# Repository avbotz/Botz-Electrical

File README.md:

# Botz-Electrical
PCBs and anything else electrical may want to leave for posterity.

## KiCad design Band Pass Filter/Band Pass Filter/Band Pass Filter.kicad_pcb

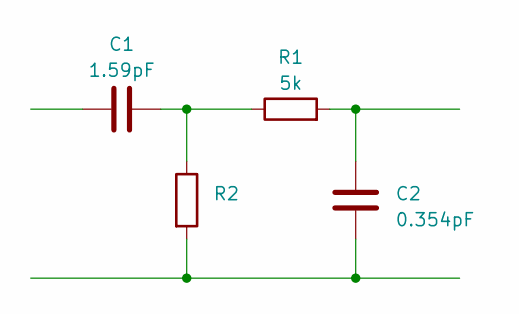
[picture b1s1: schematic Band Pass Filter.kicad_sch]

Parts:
C1: 1.59pF
C2: 0.354pF
R1, R2: 5k

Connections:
unnamed: C1.2, R1.1, R2.1
unnamed: C2.1, R1.2
unnamed: C2.2, R2.2

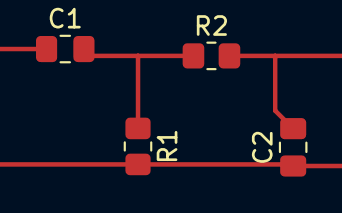
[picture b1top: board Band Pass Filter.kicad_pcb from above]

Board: 2 copper layers, 4 parts (0 on the bottom side), 3 nets.

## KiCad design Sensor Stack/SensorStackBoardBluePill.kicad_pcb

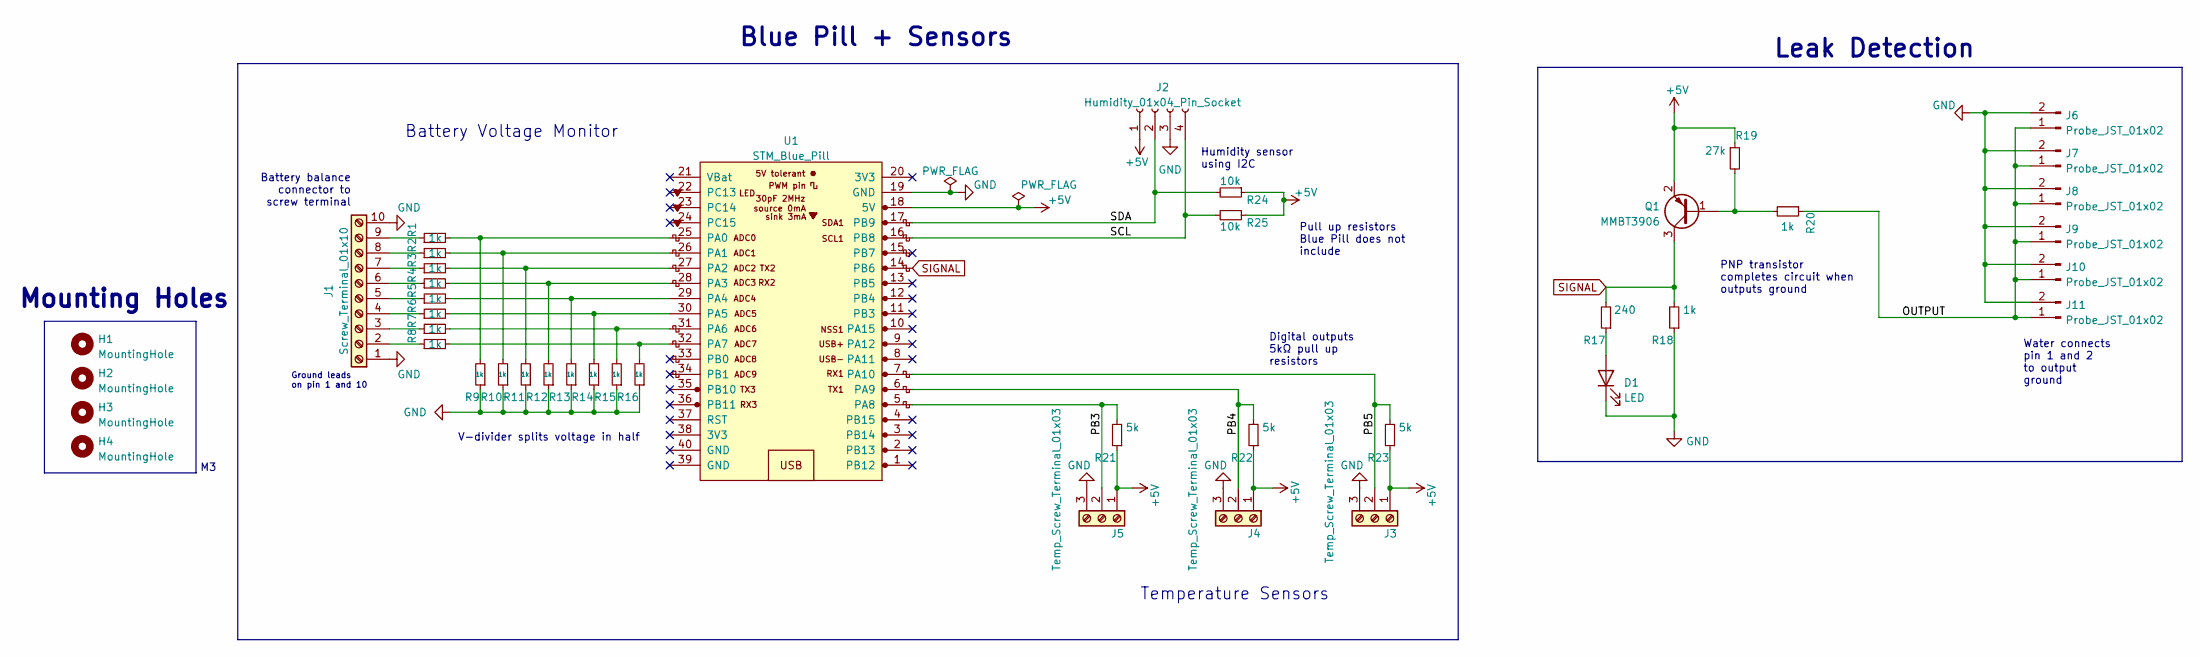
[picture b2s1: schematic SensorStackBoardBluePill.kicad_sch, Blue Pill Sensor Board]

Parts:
D1: LED; LED_0805_2012Metric_Pad1.15x1.40mm_HandSolder
H1, H2, H3, H4: MountingHole; MountingHole_3.2mm_M3
J1: Screw_Terminal_01x10; TerminalBlock_RND_205-00240_1x10_P5.08mm_Horizontal
J2: Humidity_01x04_Pin_Socket; PinSocket_1x04_P2.54mm_Vertical
J3, J4, J5: Temp_Screw_Terminal_01x03; TerminalBlock_RND_205-00233_1x03_P5.08mm_Horizontal
J6, J7, J8, J9, J10, J11: Probe_JST_01x02; JST_GH_BM02B-GHS-TBT_1x02-1MP_P1.25mm_Vertical
Q1: MMBT3906; SOT-23
R1, R2, R3, R4, R5, R6, R7, R8, R9, R10, R11, R12, R13, R14, R15, R16, R18, R20: 1k; R_0805_2012Metric_Pad1.20x1.40mm_HandSolder
R17: 240; R_0805_2012Metric_Pad1.20x1.40mm_HandSolder
R19: 27k; R_0805_2012Metric_Pad1.20x1.40mm_HandSolder
R21, R22, R23: 5k; R_0805_2012Metric_Pad1.20x1.40mm_HandSolder
R24, R25: 10k; R_0805_2012Metric_Pad1.20x1.40mm_HandSolder
U1: STM_Blue_Pill; YAAJ_BluePill_1

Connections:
+5V: J2.1, J3.1, J4.1, J5.1, Q1.2 (E), R19.1, R21.1, R22.1, R23.1, R24.1, R25.1, U1.18 (5V)
/OUTPUT: J6.1, J7.1, J8.1, J9.1, J10.1, J11.1, R20.1
/PB3: J5.2, R21.2, U1.5 (PA8)
/PB4: J4.2, R22.2, U1.6 (PA9)
/PB5: J3.2, R23.2, U1.7 (PA10)
/SCL: J2.4, R25.2, U1.16 (PB8)
/SDA: J2.2, R24.2, U1.17 (PB9)
GND: D1.1 (K), J1.1, J1.10, J2.3, J3.3, J4.3, J5.3, J6.2, J7.2, J8.2, J9.2, J10.2, J11.2, R9.1, R10.1, R11.1, R12.1, R13.1, R14.1, R15.1, R16.1, R18.1, U1.19 (GND)
unnamed: D1.2 (A), R17.1
unnamed: J1.2, R8.1
unnamed: J1.3, R7.1
unnamed: J1.4, R6.1
unnamed: J1.5, R5.1
unnamed: J1.6, R4.1
unnamed: J1.7, R3.1
unnamed: J1.8, R2.1
unnamed: J1.9, R1.1
unnamed: Q1.1 (B), R19.2, R20.2
unnamed: R1.2, R9.2, U1.25 (PA0)
unnamed: R2.2, R10.2, U1.26 (PA1)
unnamed: R3.2, R11.2, U1.27 (PA2)
unnamed: R4.2, R12.2, U1.28 (PA3)
unnamed: R5.2, R13.2, U1.29 (PA4)
unnamed: R6.2, R14.2, U1.30 (PA5)
unnamed: R7.2, R15.2, U1.31 (PA6)
unnamed: R8.2, R16.2, U1.32 (PA7)
SIGNAL: Q1.3 (C), R17.2, R18.2, U1.14 (PB6)

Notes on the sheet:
Pull up resistors Blue Pill does not include
Mounting Holes
Digital outputs 5kΩ pull up resistors
Water connects pin 1 and 2 to output ground
Humidity sensor using I2C
PNP transistor completes circuit when outputs ground
Ground leads on pin 1 and 10
Battery Voltage Monitor
V-divider splits voltage in half
Battery balance connector to screw terminal
Leak Detection
Temperature Sensors
Blue Pill + Sensors

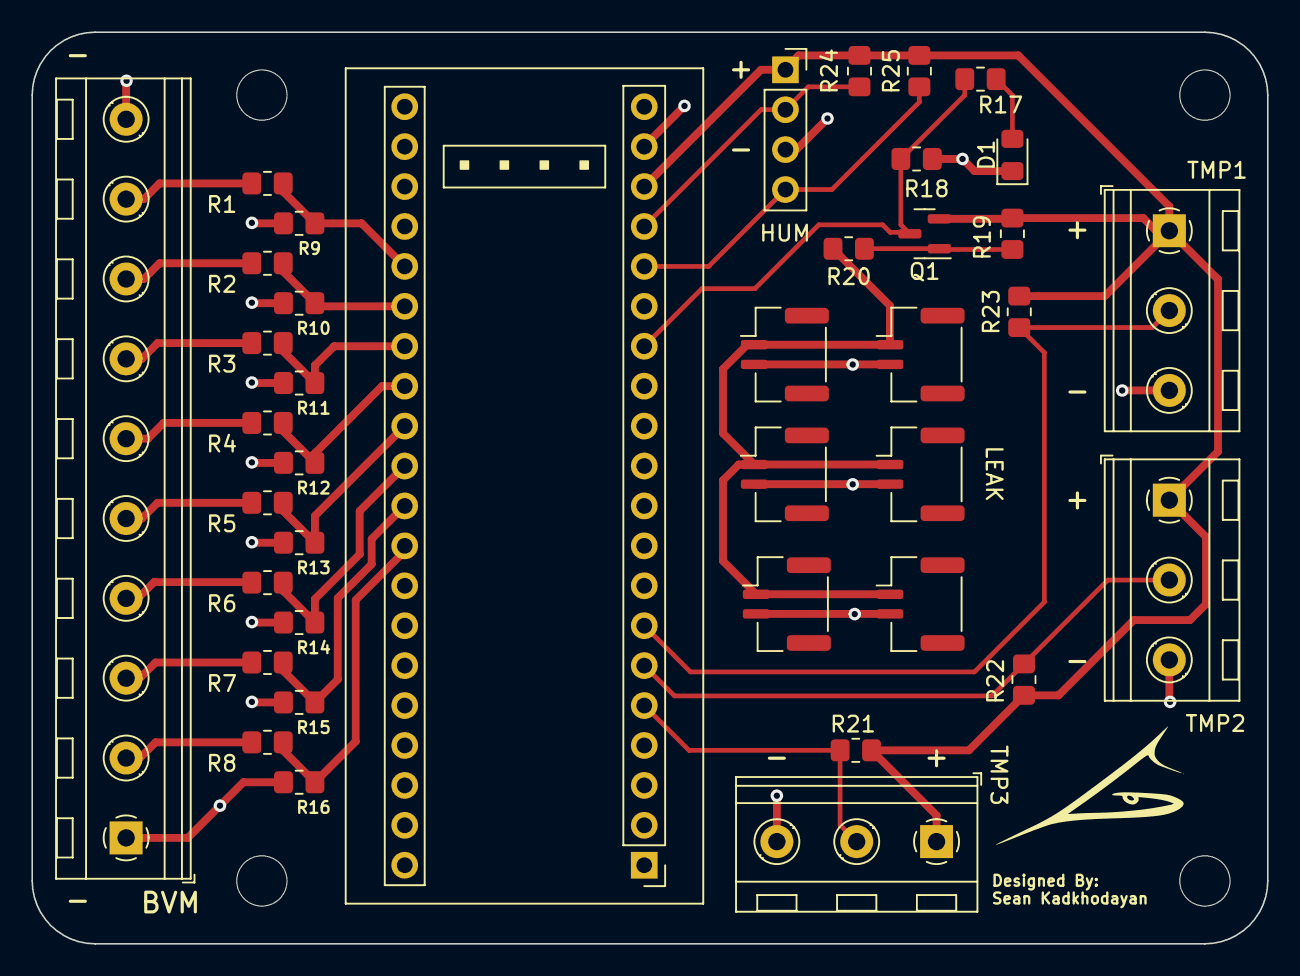
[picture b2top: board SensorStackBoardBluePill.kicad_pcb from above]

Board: 2 copper layers, 78.6 x 58.0 mm, 43 parts (0 on the bottom side), 27 nets.

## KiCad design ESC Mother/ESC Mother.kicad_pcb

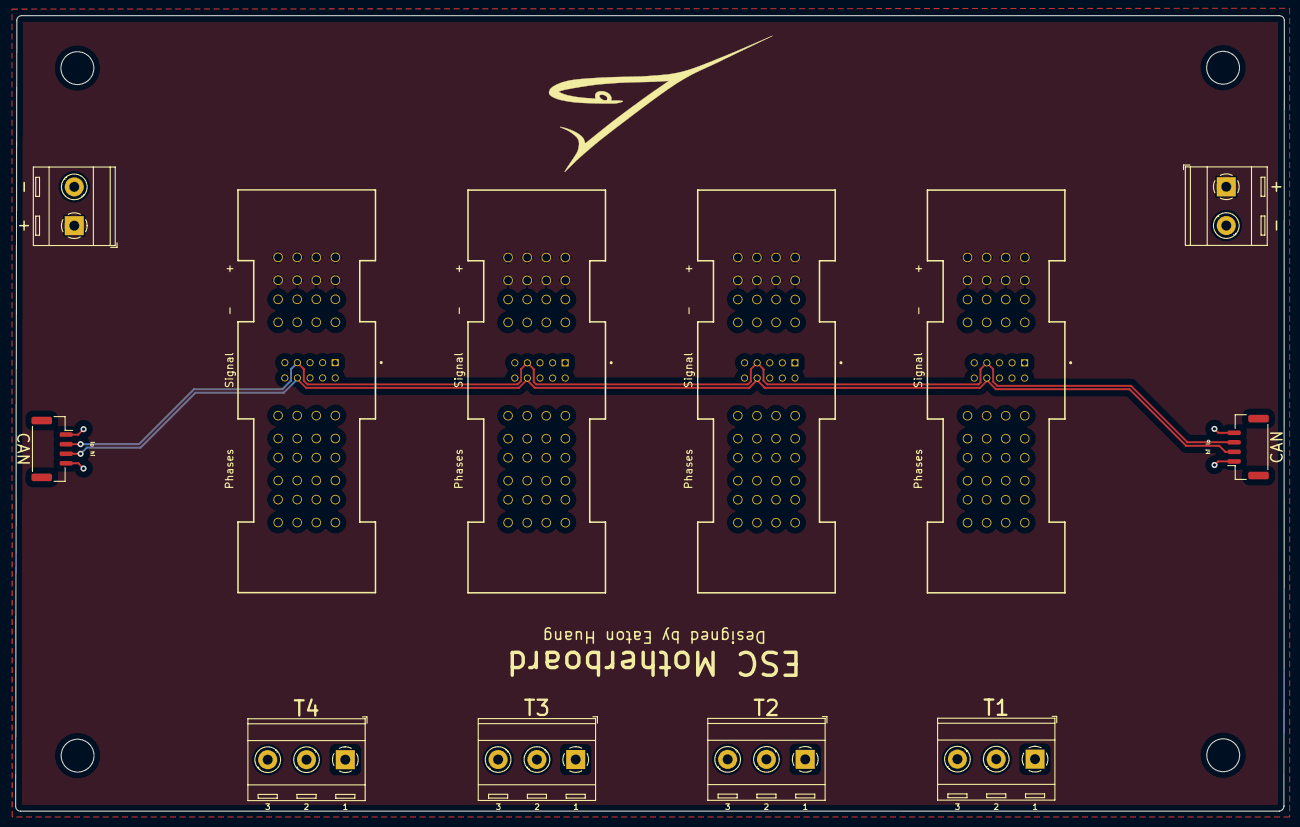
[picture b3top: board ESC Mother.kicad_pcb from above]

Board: 6 copper layers, 166.1 x 104.1 mm, 16 parts (0 on the bottom side), 17 nets.

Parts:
+: Screw_Terminal_01x02; TerminalBlock_RND_205-00287_1x02_P5.08mm_Horizontal
-: Screw_Terminal_01x02; TerminalBlock_RND_205-00287_1x02_P5.08mm_Horizontal
CAN: CAN; JST_GH_SM04B-GHS-TB_1x04-1MP_P1.25mm_Horizontal
CAN#2: CAN; JST_GH_SM04B-GHS-TB_1x04-1MP_P1.25mm_Horizontal
H1, H2, H3, H4: MountingHole; MountingHole_4.3mm_M4
J1: PWR T1; SAMTEC_ET60S-D02-5-02-D03-S-VP-S
J2: PWR T2; SAMTEC_ET60S-D02-5-02-D03-S-VP-S
J3: PWR T3; SAMTEC_ET60S-D02-5-02-D03-S-VP-S
J4: PWR T4; SAMTEC_ET60S-D02-5-02-D03-S-VP-S
T1: T1; TerminalBlock_RND_205-00288_1x03_P5.08mm_Horizontal
T2: T2; TerminalBlock_RND_205-00288_1x03_P5.08mm_Horizontal
T3: T3; TerminalBlock_RND_205-00288_1x03_P5.08mm_Horizontal
T4: T4; TerminalBlock_RND_205-00288_1x03_P5.08mm_Horizontal

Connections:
+5V: CAN.1, CAN#2.1, J1.09, J2.09, J3.09, J4.09
/16V: +.1, -.1, J1.P01_1 (P01), J1.P01_2 (P01), J1.P01_3 (P01), J1.P01_4 (P01), J1.P01_5 (P01), J1.P01_6 (P01), J1.P01_7 (P01), J1.P01_8 (P01), J2.P01_1 (P01), J2.P01_2 (P01), J2.P01_3 (P01), J2.P01_4 (P01), J2.P01_5 (P01), J2.P01_6 (P01), J2.P01_7 (P01), J2.P01_8 (P01), J3.P01_1 (P01), J3.P01_2 (P01), J3.P01_3 (P01), J3.P01_4 (P01), J3.P01_5 (P01), J3.P01_6 (P01), J3.P01_7 (P01), J3.P01_8 (P01), J4.P01_1 (P01), J4.P01_2 (P01), J4.P01_3 (P01), J4.P01_4 (P01), J4.P01_5 (P01), J4.P01_6 (P01), J4.P01_7 (P01), J4.P01_8 (P01)
/CAH: CAN.3, CAN#2.2, J1.08, J2.08, J3.08, J4.08
/CAL: CAN.2, CAN#2.3, J1.07, J2.07, J3.07, J4.07
/Phase_1_T1: J1.P05_1 (P05), J1.P05_2 (P05), J1.P05_3 (P05), J1.P05_4 (P05), J1.P05_5 (P05), J1.P05_6 (P05), J1.P05_7 (P05), J1.P05_8 (P05), T1.1
/Phase_1_T2: J2.P05_1 (P05), J2.P05_2 (P05), J2.P05_3 (P05), J2.P05_4 (P05), J2.P05_5 (P05), J2.P05_6 (P05), J2.P05_7 (P05), J2.P05_8 (P05), T2.1
/Phase_1_T3: J3.P05_1 (P05), J3.P05_2 (P05), J3.P05_3 (P05), J3.P05_4 (P05), J3.P05_5 (P05), J3.P05_6 (P05), J3.P05_7 (P05), J3.P05_8 (P05), T3.1
/Phase_1_T4: J4.P05_1 (P05), J4.P05_2 (P05), J4.P05_3 (P05), J4.P05_4 (P05), J4.P05_5 (P05), J4.P05_6 (P05), J4.P05_7 (P05), J4.P05_8 (P05), T4.1
/Phase_2_T1: J1.P04_1 (P04), J1.P04_2 (P04), J1.P04_3 (P04), J1.P04_4 (P04), J1.P04_5 (P04), J1.P04_6 (P04), J1.P04_7 (P04), J1.P04_8 (P04), T1.2
/Phase_2_T2: J2.P04_1 (P04), J2.P04_2 (P04), J2.P04_3 (P04), J2.P04_4 (P04), J2.P04_5 (P04), J2.P04_6 (P04), J2.P04_7 (P04), J2.P04_8 (P04), T2.2
/Phase_2_T3: J3.P04_1 (P04), J3.P04_2 (P04), J3.P04_3 (P04), J3.P04_4 (P04), J3.P04_5 (P04), J3.P04_6 (P04), J3.P04_7 (P04), J3.P04_8 (P04), T3.2
/Phase_2_T4: J4.P04_1 (P04), J4.P04_2 (P04), J4.P04_3 (P04), J4.P04_4 (P04), J4.P04_5 (P04), J4.P04_6 (P04), J4.P04_7 (P04), J4.P04_8 (P04), T4.2
/Phase_3_T1: J1.P03_1 (P03), J1.P03_2 (P03), J1.P03_3 (P03), J1.P03_4 (P03), J1.P03_5 (P03), J1.P03_6 (P03), J1.P03_7 (P03), J1.P03_8 (P03), T1.3
/Phase_3_T2: J2.P03_1 (P03), J2.P03_2 (P03), J2.P03_3 (P03), J2.P03_4 (P03), J2.P03_5 (P03), J2.P03_6 (P03), J2.P03_7 (P03), J2.P03_8 (P03), T2.3
/Phase_3_T3: J3.P03_1 (P03), J3.P03_2 (P03), J3.P03_3 (P03), J3.P03_4 (P03), J3.P03_5 (P03), J3.P03_6 (P03), J3.P03_7 (P03), J3.P03_8 (P03), T3.3
/Phase_3_T4: J4.P03_1 (P03), J4.P03_2 (P03), J4.P03_3 (P03), J4.P03_4 (P03), J4.P03_5 (P03), J4.P03_6 (P03), J4.P03_7 (P03), J4.P03_8 (P03), T4.3
GND: +.2, -.2, CAN.4, CAN#2.4, J1.10, J1.P02_1 (P02), J1.P02_2 (P02), J1.P02_3 (P02), J1.P02_4 (P02), J1.P02_5 (P02), J1.P02_6 (P02), J1.P02_7 (P02), J1.P02_8 (P02), J2.10, J2.P02_1 (P02), J2.P02_2 (P02), J2.P02_3 (P02), J2.P02_4 (P02), J2.P02_5 (P02), J2.P02_6 (P02), J2.P02_7 (P02), J2.P02_8 (P02), J3.10, J3.P02_1 (P02), J3.P02_2 (P02), J3.P02_3 (P02), J3.P02_4 (P02), J3.P02_5 (P02), J3.P02_6 (P02), J3.P02_7 (P02), J3.P02_8 (P02), J4.10, J4.P02_1 (P02), J4.P02_2 (P02), J4.P02_3 (P02), J4.P02_4 (P02), J4.P02_5 (P02), J4.P02_6 (P02), J4.P02_7 (P02), J4.P02_8 (P02)

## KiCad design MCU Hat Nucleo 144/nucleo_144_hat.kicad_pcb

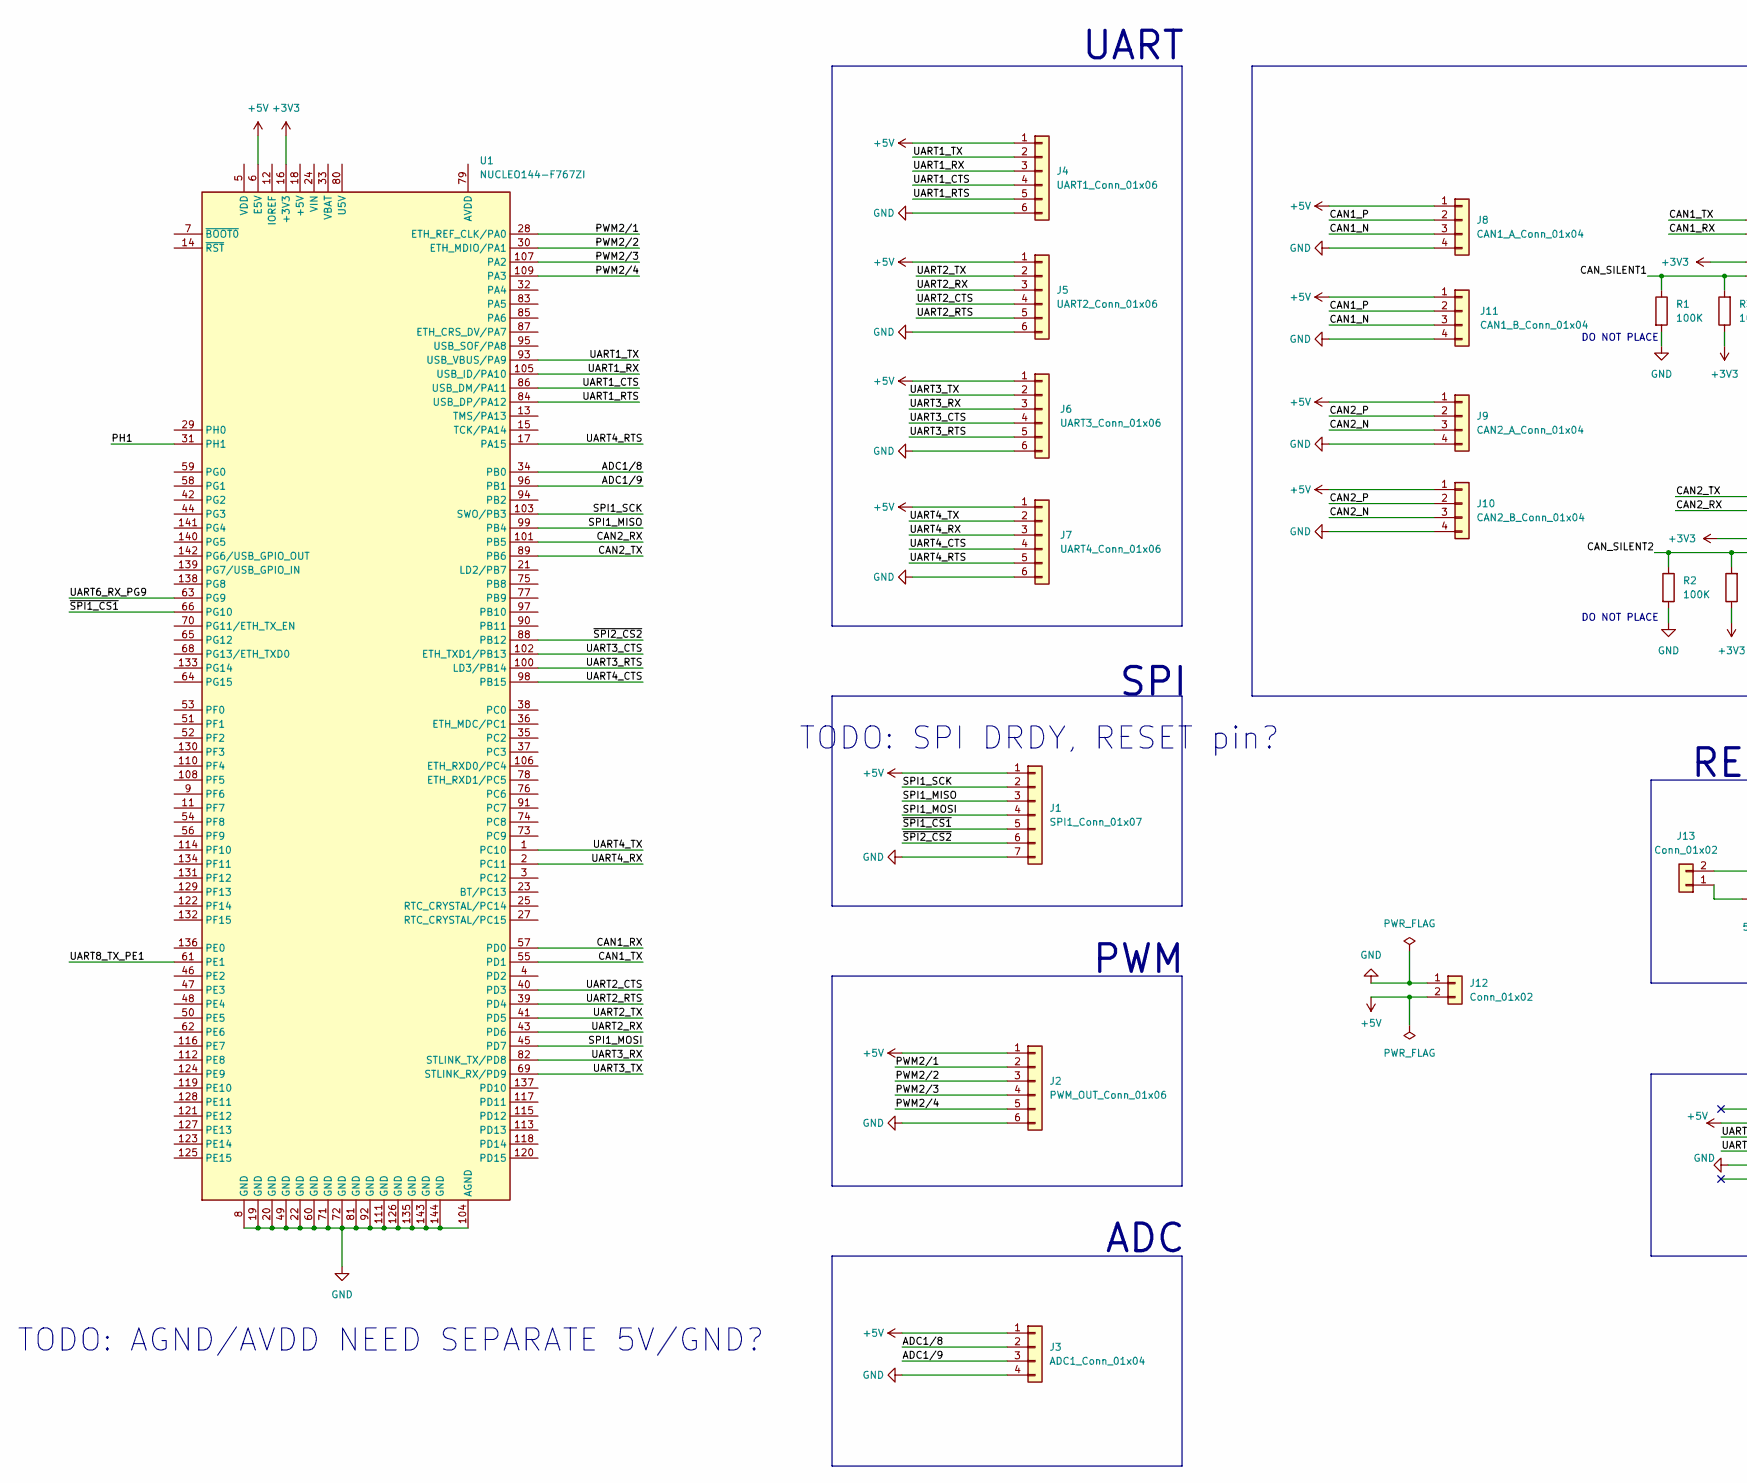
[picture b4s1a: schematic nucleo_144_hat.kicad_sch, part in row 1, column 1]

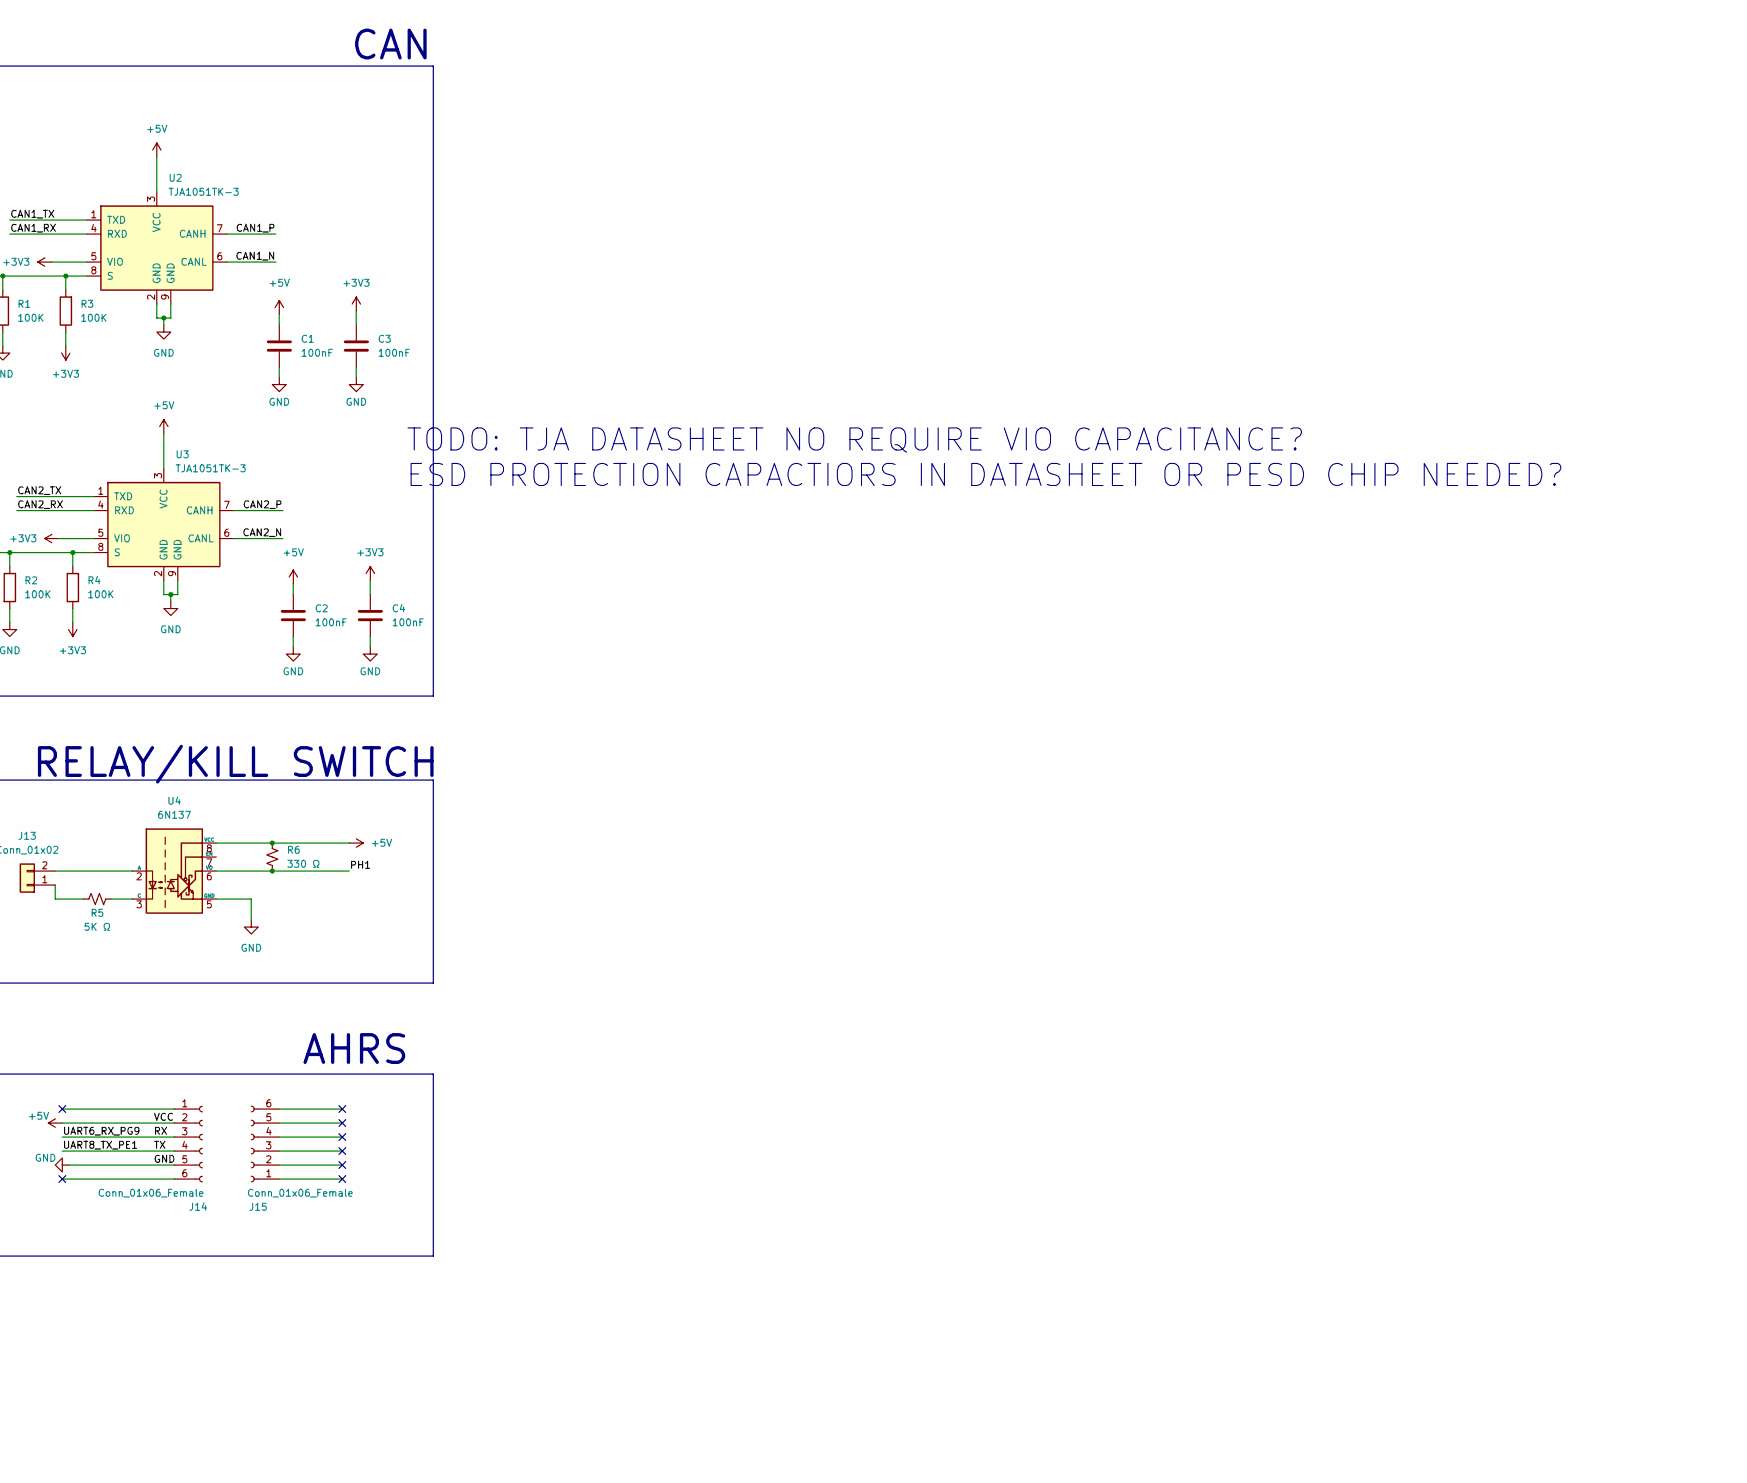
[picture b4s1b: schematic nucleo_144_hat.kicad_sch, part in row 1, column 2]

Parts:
C1, C2, C3, C4: 100nF; C_0805_2012Metric_Pad1.18x1.45mm_HandSolder
J1: SPI1_Conn_01x07; JST_GH_BM07B-GHS-TBT_1x07-1MP_P1.25mm_Vertical
J2: PWM_OUT_Conn_01x06; JST_GH_BM06B-GHS-TBT_1x06-1MP_P1.25mm_Vertical
J3: ADC1_Conn_01x04; JST_GH_SM04B-GHS-TB_1x04-1MP_P1.25mm_Horizontal
J4: UART1_Conn_01x06; JST_GH_BM06B-GHS-TBT_1x06-1MP_P1.25mm_Vertical
J5: UART2_Conn_01x06; JST_GH_BM06B-GHS-TBT_1x06-1MP_P1.25mm_Vertical
J6: UART3_Conn_01x06; JST_GH_BM06B-GHS-TBT_1x06-1MP_P1.25mm_Vertical
J7: UART4_Conn_01x06; JST_GH_BM06B-GHS-TBT_1x06-1MP_P1.25mm_Vertical
J8: CAN1_A_Conn_01x04; JST_GH_SM04B-GHS-TB_1x04-1MP_P1.25mm_Horizontal
J9: CAN2_A_Conn_01x04; JST_GH_SM04B-GHS-TB_1x04-1MP_P1.25mm_Horizontal
J10: CAN2_B_Conn_01x04; JST_GH_SM04B-GHS-TB_1x04-1MP_P1.25mm_Horizontal
J11: CAN1_B_Conn_01x04; JST_GH_SM04B-GHS-TB_1x04-1MP_P1.25mm_Horizontal
J12: Conn_01x02; Molex_CLIK-Mate_502386-0270_1x02-1MP_P1.25mm_Horizontal
J13: Conn_01x02; JST_GH_BM02B-GHS-TBT_1x02-1MP_P1.25mm_Vertical
J14, J15: Conn_01x06_Female; PinSocket_1x06_P2.54mm_Vertical
R1, R2, R3, R4: 100K; R_0805_2012Metric_Pad1.20x1.40mm_HandSolder
R5: 5K Ω; R_0805_2012Metric_Pad1.20x1.40mm_HandSolder
R6: 330 Ω; R_0805_2012Metric_Pad1.20x1.40mm_HandSolder
U1: NUCLEO144-F767ZI; nucleo144_hat
U2, U3: TJA1051TK-3; DFN-8-1EP_3x3mm_P0.65mm_EP1.55x2.4mm
U4: 6N137; DIP-8_W7.62mm

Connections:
+3V3: C3.1, C4.1, R3.1, R4.1, U1.16 (+3V3), U2.5 (VIO), U3.5 (VIO)
+5V: C1.1, C2.1, J1.1, J2.1, J3.1, J4.1, J5.1, J6.1, J7.1, J8.1, J9.1, J10.1, J11.1, J12.2, J14.2, R6.1, U1.6 (E5V), U2.3 (VCC), U3.3 (VCC), U4.8 (VCC)
/ADC1/8: J3.2, U1.34 (PB0)
/ADC1/9: J3.3, U1.96 (PB1)
/CAN1_N: J8.3, J11.3, U2.6 (CANL)
/CAN1_P: J8.2, J11.2, U2.7 (CANH)
/CAN1_RX: U1.57 (PD0), U2.4 (RXD)
/CAN1_TX: U1.55 (PD1), U2.1 (TXD)
/CAN2_N: J9.3, J10.3, U3.6 (CANL)
/CAN2_P: J9.2, J10.2, U3.7 (CANH)
/CAN2_RX: U1.101 (PB5), U3.4 (RXD)
/CAN2_TX: U1.89 (PB6), U3.1 (TXD)
/CAN_SILENT1: R1.1, R3.2, U2.8 (S)
/CAN_SILENT2: R2.1, R4.2, U3.8 (S)
/PH1: R6.2, U1.31 (PH1), U4.6 (VO)
/PWM2/1: J2.2, U1.28 (ETH_REF_CLK/PA0)
/PWM2/2: J2.3, U1.30 (ETH_MDIO/PA1)
/PWM2/3: J2.4, U1.107 (PA2)
/PWM2/4: J2.5, U1.109 (PA3)
/RX: J14.3, U1.63 (PG9)
/SPI1_MISO: J1.3, U1.99 (PB4)
/SPI1_MOSI: J1.4, U1.45 (PD7)
/SPI1_SCK: J1.2, U1.103 (SWO/PB3)
/TX: J14.4, U1.61 (PE1)
/UART1_CTS: J4.4, U1.86 (USB_DM/PA11)
/UART1_RTS: J4.5, U1.84 (USB_DP/PA12)
/UART1_RX: J4.3, U1.105 (USB_ID/PA10)
/UART1_TX: J4.2, U1.93 (USB_VBUS/PA9)
/UART2_CTS: J5.4, U1.40 (PD3)
/UART2_RTS: J5.5, U1.39 (PD4)
/UART2_RX: J5.3, U1.43 (PD6)
/UART2_TX: J5.2, U1.41 (PD5)
/UART3_CTS: J6.4, U1.102 (ETH_TXD1/PB13)
/UART3_RTS: J6.5, U1.100 (LD3/PB14)
/UART3_RX: J6.3, U1.82 (STLINK_TX/PD8)
/UART3_TX: J6.2, U1.69 (STLINK_RX/PD9)
/UART4_CTS: J7.4, U1.98 (PB15)
/UART4_RTS: J7.5, U1.17 (PA15)
/UART4_RX: J7.3, U1.2 (PC11)
/UART4_TX: J7.2, U1.1 (PC10)
/~SPI1_CS1: J1.5, U1.66 (PG10)
/~SPI2_CS2: J1.6, U1.88 (PB12)
GND: C1.2, C2.2, C3.2, C4.2, J1.7, J2.6, J3.4, J4.6, J5.6, J6.6, J7.6, J8.4, J9.4, J10.4, J11.4, J12.1, J14.5, R1.2, R2.2, U1.8 (GND), U1.19 (GND), U1.20 (GND), U1.22 (GND), U1.49 (GND), U1.60 (GND), U1.71 (GND), U1.72 (GND), U1.81 (GND), U1.92 (GND), U1.104 (AGND), U1.111 (GND), U1.126 (GND), U1.135 (GND), U1.143 (GND), U1.144 (GND), U2.2 (GND), U2.9 (GND), U3.2 (GND), U3.9 (GND), U4.5 (GND)
unnamed: J13.1, R5.1
unnamed: J13.2, U4.2 (A)
unnamed: R5.2, U4.3 (C)

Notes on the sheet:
TODO: AGND/AVDD NEED SEPARATE 5V/GND?
DO NOT PLACE
RELAY/KILL SWITCH
PWM
TODO: TJA DATASHEET NO REQUIRE VIO CAPACITANCE? ESD PROTECTION CAPACTIORS IN DATASHEET OR PESD CHIP NEEDED?
ADC
SPI
TODO: SPI DRDY, RESET pin?
CAN
AHRS
UART

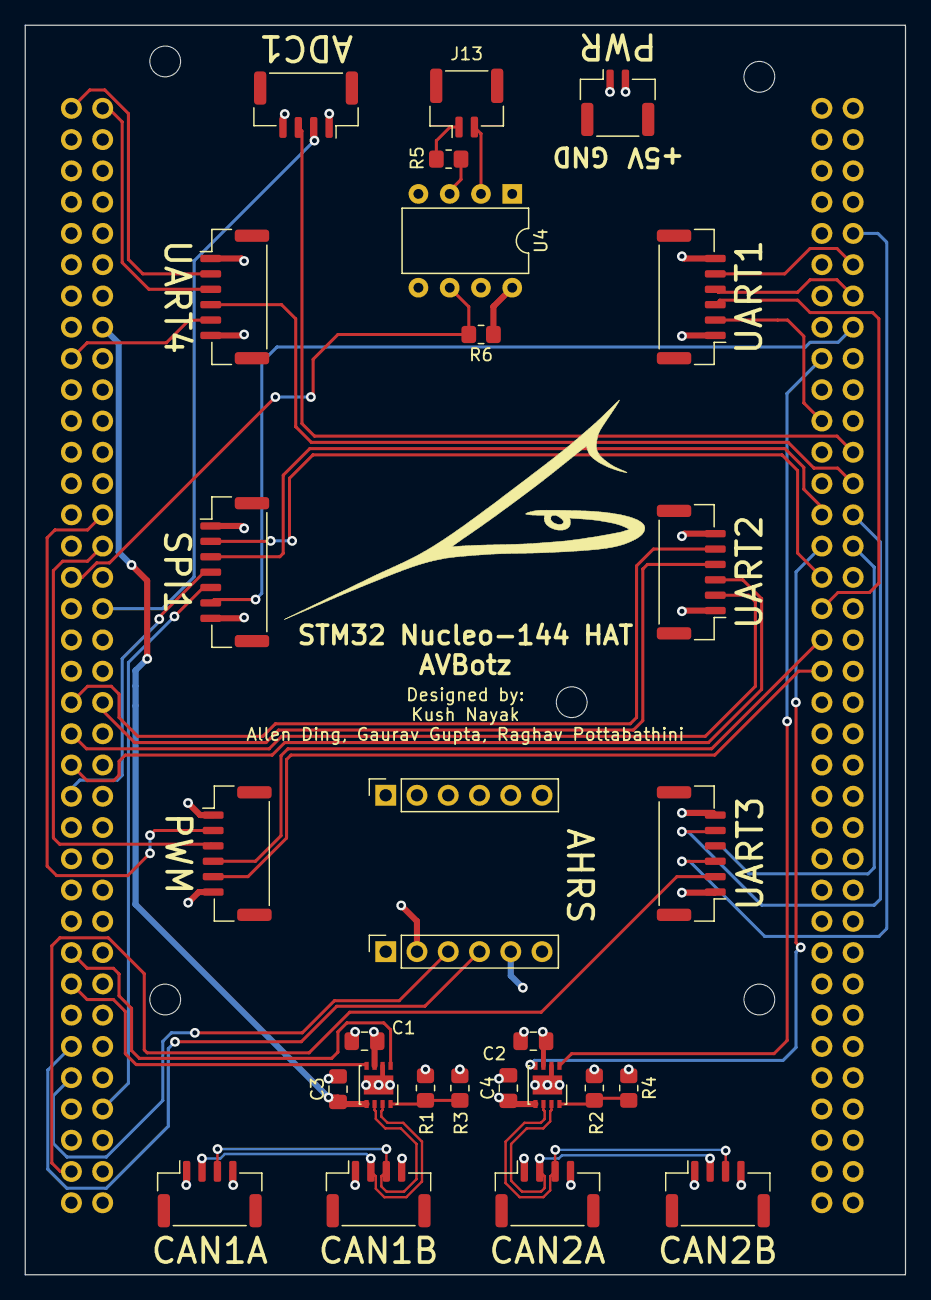
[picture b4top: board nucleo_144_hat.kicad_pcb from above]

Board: 4 copper layers, 71.5 x 101.5 mm, 29 parts (0 on the bottom side), 46 nets.

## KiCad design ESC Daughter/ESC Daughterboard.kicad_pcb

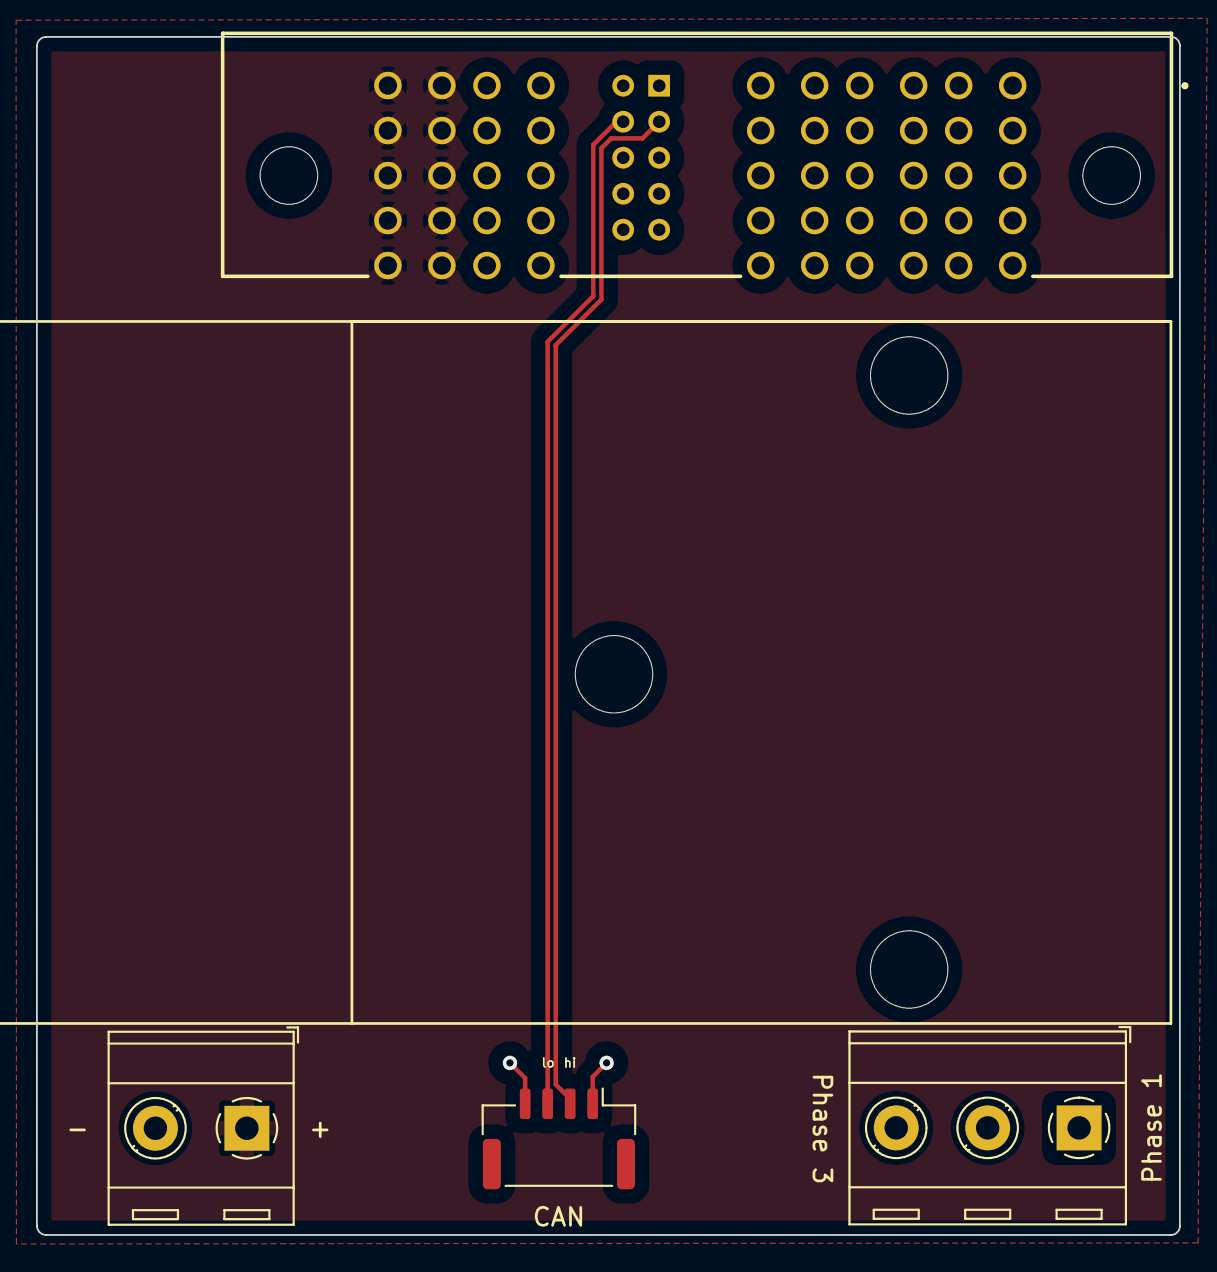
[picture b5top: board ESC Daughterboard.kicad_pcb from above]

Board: 6 copper layers, 63.5 x 66.6 mm, 7 parts (0 on the bottom side), 8 nets.

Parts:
CAN: Conn_01x04; JST_GH_BM04B-GHS-TBT_1x04-1MP_P1.25mm_Vertical
H1, H2, H3: MountingHole; MountingHole_4.3mm_M4
J2: Screw_Terminal_01x02; TerminalBlock_RND_205-00287_1x02_P5.08mm_Horizontal
J5: ET60T; SAMTEC_ET60T-D03-5-02-D02-X-R1-S
Phase 1: Screw_Terminal_01x03; TerminalBlock_RND_205-00288_1x03_P5.08mm_Horizontal

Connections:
+5V: CAN.1, J5.02
/16V: J2.1, J5.P05_1 (P05), J5.P05_2 (P05), J5.P05_3 (P05), J5.P05_4 (P05), J5.P05_5 (P05), J5.P05_6 (P05), J5.P05_7 (P05), J5.P05_8 (P05), J5.P05_9 (P05), J5.P05_10 (P05)
/CAH: CAN.2, J5.03
/CAL: CAN.3, J5.04
/Phase_1: J5.P01_1 (P01), J5.P01_2 (P01), J5.P01_3 (P01), J5.P01_4 (P01), J5.P01_5 (P01), J5.P01_6 (P01), J5.P01_7 (P01), J5.P01_8 (P01), J5.P01_9 (P01), J5.P01_10 (P01), Phase 1.1
/Phase_2: J5.P02_1 (P02), J5.P02_2 (P02), J5.P02_3 (P02), J5.P02_4 (P02), J5.P02_5 (P02), J5.P02_6 (P02), J5.P02_7 (P02), J5.P02_8 (P02), J5.P02_9 (P02), J5.P02_10 (P02), Phase 1.2
/Phase_3: J5.P03_1 (P03), J5.P03_2 (P03), J5.P03_3 (P03), J5.P03_4 (P03), J5.P03_5 (P03), J5.P03_6 (P03), J5.P03_7 (P03), J5.P03_8 (P03), J5.P03_9 (P03), J5.P03_10 (P03), Phase 1.3
GND: CAN.4, J2.2, J5.01, J5.P04_1 (P04), J5.P04_2 (P04), J5.P04_3 (P04), J5.P04_4 (P04), J5.P04_5 (P04), J5.P04_6 (P04), J5.P04_7 (P04), J5.P04_8 (P04), J5.P04_9 (P04), J5.P04_10 (P04)

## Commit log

2023-02-19 Created band pass filter
2023-02-19 Started making PCB
